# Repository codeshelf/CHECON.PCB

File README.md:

CHECON.PCB
==========

CHE controller PCB design files (No production files/ Brain mounts to this with scanner / PosCon interface etc)

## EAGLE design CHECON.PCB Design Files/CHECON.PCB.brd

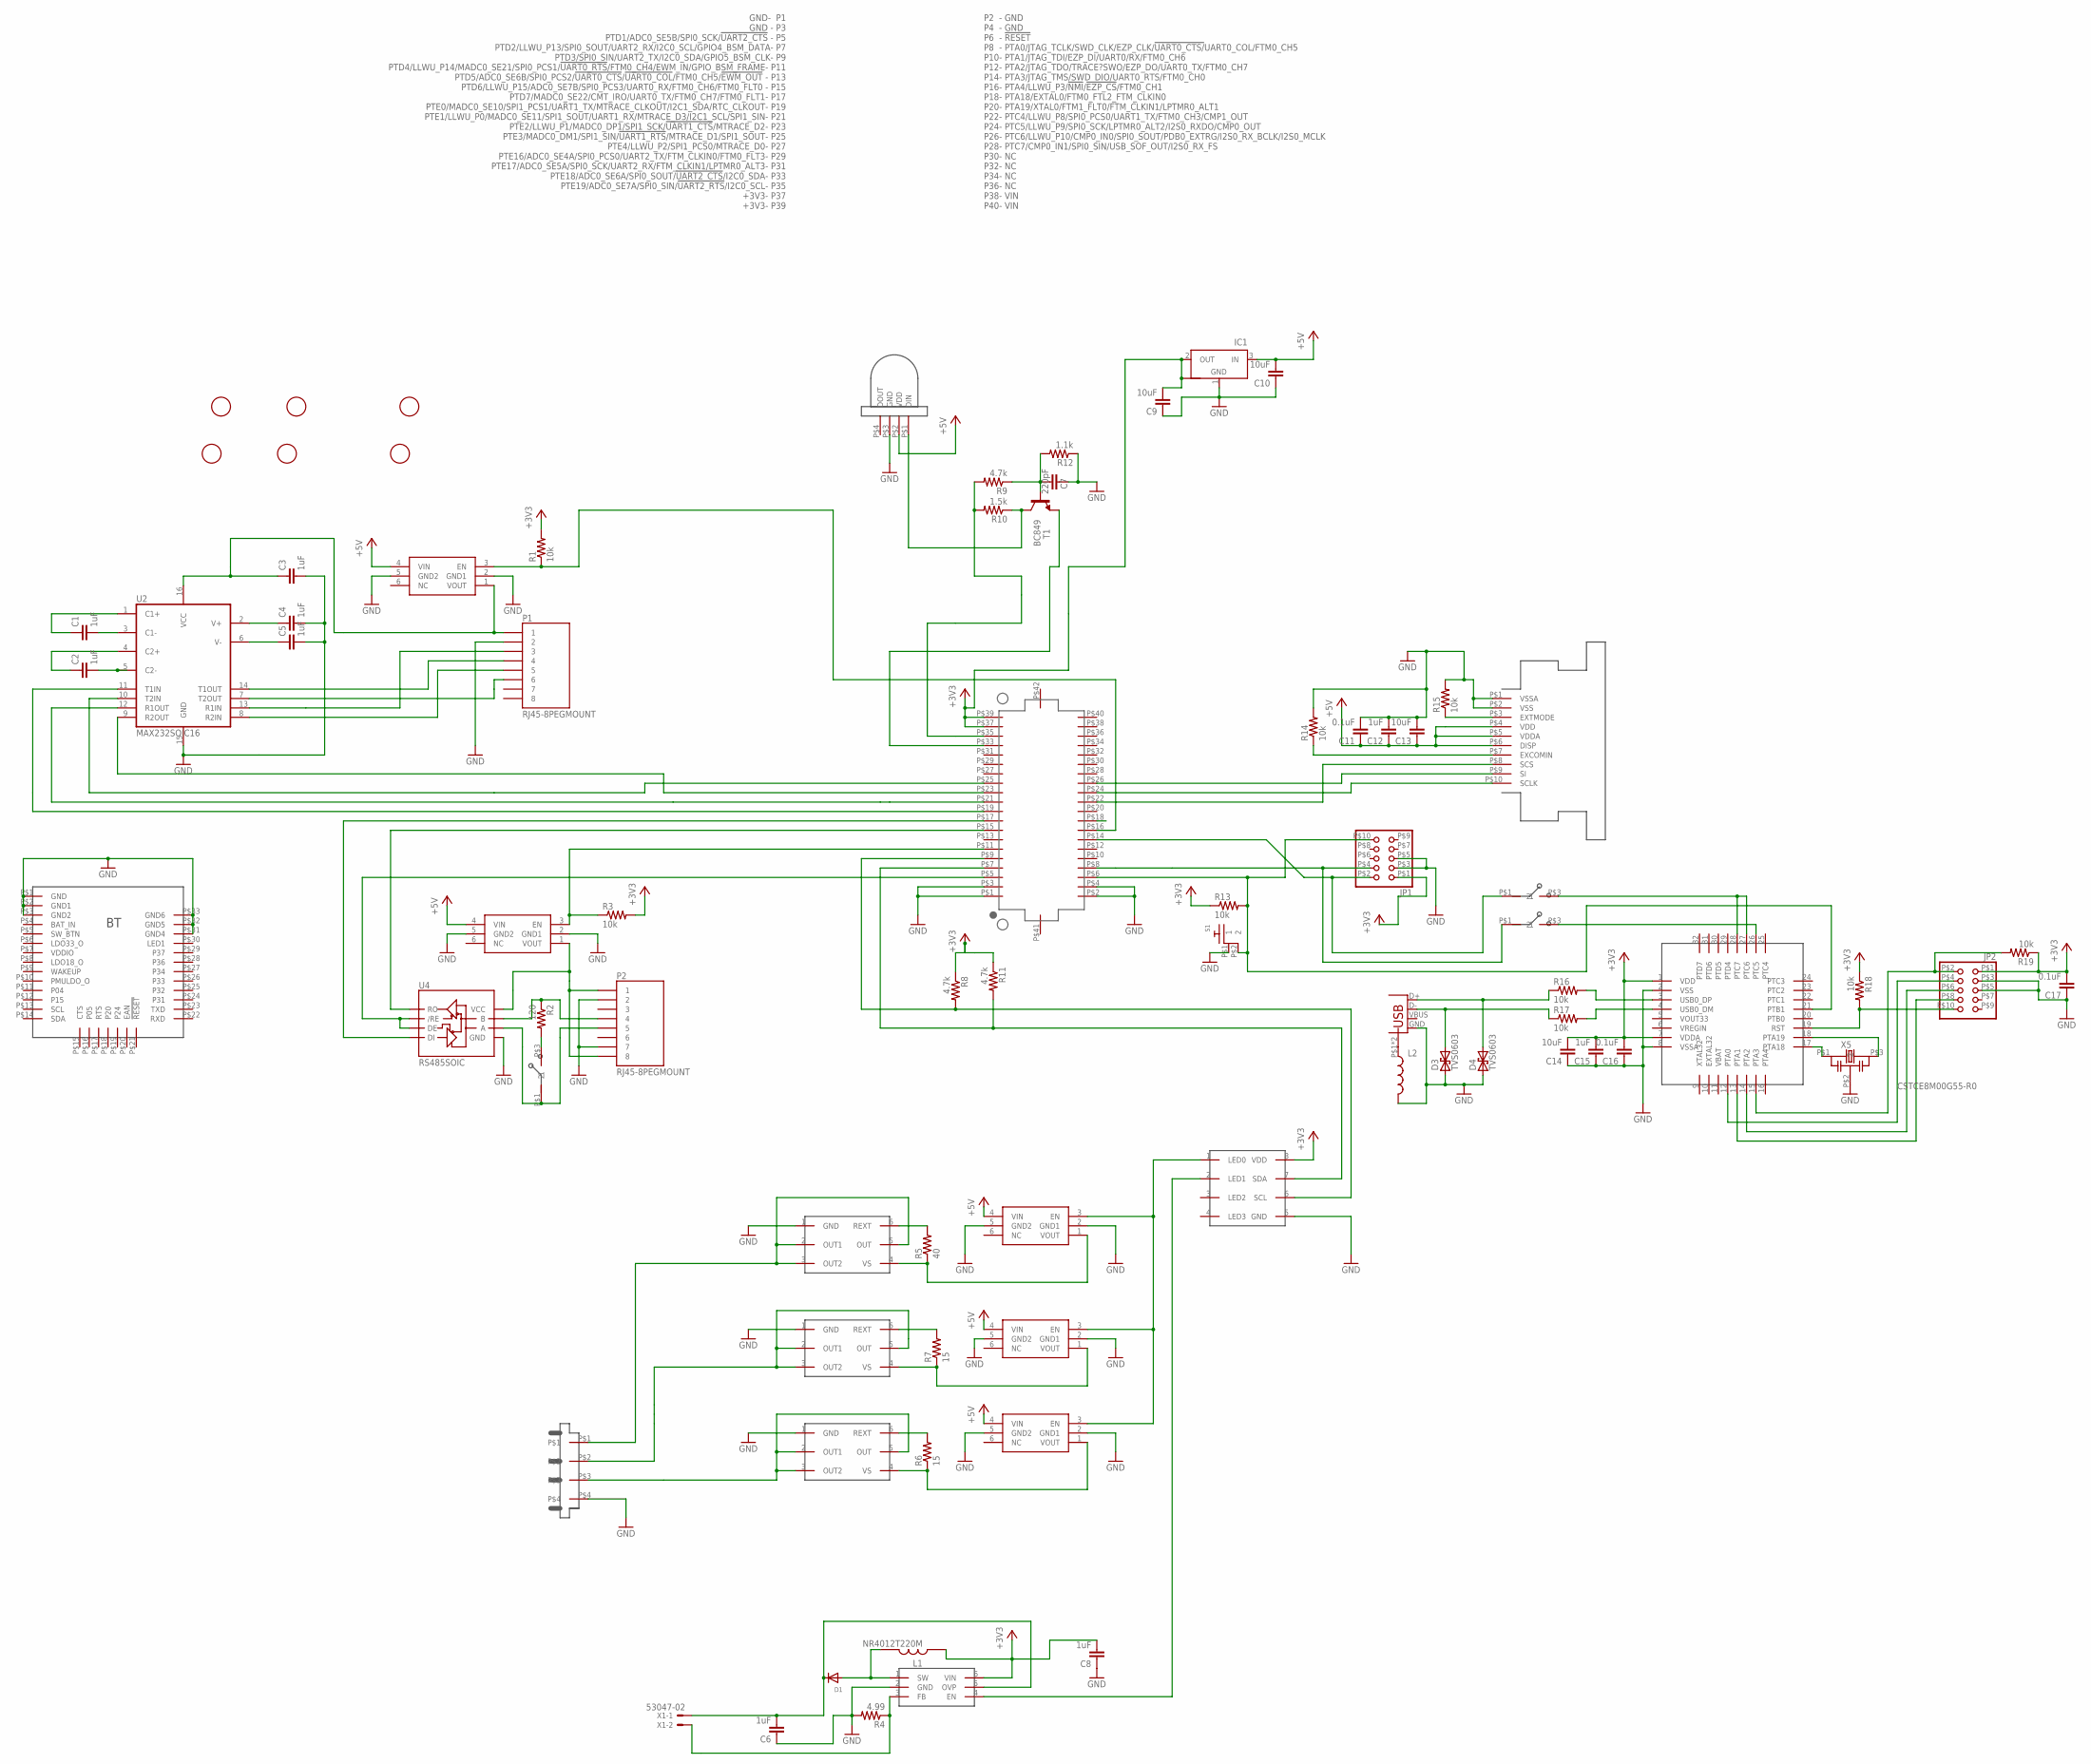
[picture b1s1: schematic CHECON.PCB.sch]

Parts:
C1, C2, C3, C4, C5, C6, C8, C12, C15: 1uF; C0805
C7: 220pF; C0805
C9, C10, C13, C14: 10uF; C0805
C11, C16, C17: 0.1uF; C0805
D1: DIODESOD-523; SOD-523
D2: LED_PTH_2812
D3, D4: TVS0603; 0603-RES
F1, F2, F3, F4, F5, F6: FIDUCIAL; FIDUCIAL_1MM
IC1: NCP1117ST33T3G_1; SOT223
J1: 2.7_BL_CONN; XD2B-0406-26A
J2: USB_B; USB-B-PTH-VERTICAL
J3: 52745-1097
JP1, JP2: PINHD-2X5SMALL; 2X5HDR
L1: NR4012T220M
L2: INDUCTOR0603; 0603
P1, P2: RJ45-8PEGMOUNT; MOLEX-0955016889
R1, R3, R13, R14, R15, R16, R17, R18, R19: 10k; RF-C0805
R2: 120; RF-C0805
R4: 4.99; RF-C0805
R5: 40; RF-C0805
R6, R7: 15; RF-C0805
R8, R9, R11: 4.7k; RF-C0805
R10: 1.5k; RF-C0805
R12: 1.1k; RF-C0805
S1: RA_BUTTON
SW1, SW2, SW3: CJS
T1: BC849; SOT23
U1: BM78
U2: MAX232SOIC16; SO016
U3, U5, U7, U8, U9: MIC94061C6; SC70-6L
U4: RS485SOIC; SO08
U6: AP5724; SOT23-6
U10: KW2_CPU_OFFSET; BRAIN_OFFSET
U11: PCA9632DP1; TSSOP-8
U12: KL20; QFN-32-NOPAD
X1: 53047-02
X2, X3, X4: BCR401U; SOT23-6
X5: CSTCE8M00G55-R0; CSTCE_G_A

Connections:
+3V3: C8.2, C9.2, C14.2, C15.2, C16.2, C17.2, IC1.2 (OUT), IC1.4 (OUT1), JP1.P$1 (1), JP2.P$1 (1), L1.P$2 (2), R1.2, R3.2, R8.1, R11.1, R13.1, R18.1, R19.1, U6.6 (VIN), U10.P$37 (+3V3), U10.P$39 (+3V3), U11.8 (VDD), U12.1 (VDD), U12.7 (VDDA)
+5V: C10.2, D2.P$2 (VDD), IC1.3 (IN), U7.4 (VIN), U8.4 (VIN), U9.4 (VIN)
C1: C1.1, U2.1 (C1+)
C2: C2.1, U2.4 (C2+)
GND: C3.2, C4.2, C5.2, C6.1, C7.1, C8.1, C9.1, C10.1, C11.2, C12.2, C13.2, C14.1, C15.1, C16.1, C17.1, D2.P$3 (GND), D3.1, D4.1, IC1.1 (GND), J1.P$4, J2.GND, J3.P$1 (VSSA), J3.P$2 (VSS), JP1.P$3 (3), JP1.P$5 (5), JP2.P$3 (3), JP2.P$5 (5), L2.2, P1.P$2 (2), P2.P$2 (2), P2.P$7 (7), R4.2, R12.1, R14.2, R15.2, S1.P$1 (1), U1.P$1 (GND), U1.P$2 (GND1), U1.P$3 (GND2), U1.P$31 (GND4), U1.P$32 (GND5), U1.P$33 (GND6), U2.15 (GND), U3.2 (GND1), U3.5 (GND2), U4.5 (GND), U5.2 (GND1), U5.5 (GND2), U6.2 (GND), U7.2 (GND1), U7.5 (GND2), U8.2 (GND1), U8.5 (GND2), U9.2 (GND1), U9.5 (GND2), U10.P$1 (GND), U10.P$2 (GND), U10.P$3 (GND), U10.P$4 (GND), U11.5 (GND), U12.2 (VSS), U12.8 (VSSA), X2.1 (GND), X3.1 (GND), X4.1 (GND), X5.P$2 (2)
unnamed: SW2.P$3 (2), U12.27 (PTC6), U12.28 (PTC7)
unnamed: U6.4 (EN), U11.2 (LED1)
unnamed: R4.1, U6.3 (FB), X1.2
unnamed: U12.17 (PTA18), X5.P$1 (1)
unnamed: J2.P$1 (SHIELD), J2.P$2 (SHIELD), L2.1
unnamed: U12.18 (PTA19), X5.P$3 (3)
unnamed: P1.P$6 (6), U2.7 (T2OUT)
unnamed: J1.P$1, X2.2 (OUT1), X2.3 (OUT2), X2.5 (OUT)
unnamed: U2.12 (R1OUT), U10.P$21 (PTE1/LLWU_P0/MADC0_SE11/SPI1_SOUT/UART1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)
unnamed: R9.2, R10.2, U10.P$35 (PTE19/ADC0_SE7A/SPI0_SIN/!UART2_RTS!/I2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)
unnamed: P1.P$4 (4), U2.14 (T1OUT)
unnamed: R6.1, U9.1 (VOUT), X4.4 (VS)
unnamed: R7.1, U8.1 (VOUT), X3.4 (VS)
unnamed: R5.1, U7.1 (VOUT), X2.4 (VS)
unnamed: T1.2 (E), U10.P$33 (PTE18/ADC0_SE6A/SPI0_SOUT/!UART2_CTS!/I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)
unnamed: U4.1 (RO), U10.P$15 (PTD6/LLWU_P15/ADC0_SE7B/SPI0_PCS3/UART0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)
unnamed: C1.2, U2.3 (C1-)
unnamed: P2.P$4 (4), R2.1, U4.7 (B)
unnamed: P2.P$5 (5), SW1.P$1 (1), U4.6 (A)
unnamed: C2.2, U2.5 (C2-)
unnamed: C5.1, U2.6 (V-)
unnamed: C4.1, U2.2 (V+)
unnamed: R16.2, U12.3 (USB0_DP)
unnamed: C3.1, P1.P$1 (1), U2.16 (VCC), U3.1 (VOUT)
unnamed: U2.11 (T1IN), U10.P$19 (PTE0/MADC0_SE10/SPI1_PCS1/UART1_TX/MTRA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)
unnamed: U4.4 (DI), U10.P$17 (PTD7/MADC0_SE22/CMT_IRO/UART0_TX/FTM0_C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)
unnamed: U4.2 (/RE), U4.3 (DE), U10.P$5 (PTD1/ADC0_SE5B/SPI0_SCK/!UART2_CTS)
unnamed: J3.P$9 (SI), U10.P$26 (PTC6/LLWU_P10/CMP0_IN0/SPI0_SOUT/PDB0_E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)
unnamed: J3.P$10 (SCLK), U10.P$24 (PTC5/LLWU_P8/SPI0_PCS0/UART1_TX/FTM0_CH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)
unnamed: J3.P$8 (SCS), U10.P$22 (PTC4/LLWU_P8/SPI0_PCS0/UART1_TX/FTM0_CH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)
unnamed: J3.P$3 (EXTMODE), R15.1
unnamed: J3.P$7 (EXCOMIN), R14.1
unnamed: P1.P$5 (5), U2.8 (R2IN)
unnamed: D3.2, J2.D-, R17.1
unnamed: D4.2, J2.D+, R16.1
unnamed: R6.2, X4.6 (REXT)
unnamed: U2.9 (R2OUT), U10.P$23 (PTE2/LLWU_P1/MADC0_DP1/SPI1_SCK/!UART1_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)
unnamed: R3.1, U5.3 (EN), U10.P$11 (PTD4/LLWU_P14/MADC0_SE21/SPI0_PCS1/!UAR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)
unnamed: R1.1, U3.3 (EN), U10.P$16 (PTA4/LLWU_P3/!NMI!/!EZP_CS!/FTM0_CH1)
unnamed: U2.10 (T2IN), U10.P$25 (PTE3/MADC0_DM1/SPI1_SIN/!UART1_RTS!/MTR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)
unnamed: R7.2, X3.6 (REXT)
unnamed: R5.2, X2.6 (REXT)
unnamed: U7.3 (EN), U8.3 (EN), U9.3 (EN), U11.1 (LED0)
unnamed: R11.2, U10.P$7 (PTD2/LLWU_P13/SPI0_SOUT/UART2_RX/I2C0_S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), U11.7 (SDA)
unnamed: R8.2, U10.P$9 (PTD3/SPI0_SIN/UART2_TX/I2C0_SDA/GPIO5_B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), U11.6 (SCL)
unnamed: D2.P$1 (DIN), R10.1, T1.3 (C)
unnamed: C7.2, R9.1, R12.2, T1.1 (B)
unnamed: D1.A, L1.P$1 (1), U6.1 (SW)
unnamed: J1.P$3, X4.2 (OUT1), X4.3 (OUT2), X4.5 (OUT)
unnamed: JP2.P$2 (2), R19.2, U12.15 (PTA3)
unnamed: J1.P$2, X3.2 (OUT1), X3.3 (OUT2), X3.5 (OUT)
unnamed: C6.2, D1.K (C), U6.5 (OVP), X1.1
unnamed: JP2.P$4 (4), U12.12 (PTA0)
unnamed: JP2.P$6 (6), U12.14 (PTA2)
unnamed: JP2.P$8 (8), U12.13 (PTA1)
unnamed: JP2.P$10 (10), R18.2, U12.19 (RST)
unnamed: R2.2, SW1.P$3 (2)
unnamed: R17.2, U12.4 (USB0_DM)
R1IN: P1.P$3 (3), U2.13 (R1IN)
RST: JP1.P$10 (10), R13.2, S1.P$2 (2), U10.P$6 (!RESET), U12.21 (PTB1)
SWD_CLK: JP1.P$4 (4), SW3.P$1 (1), U10.P$8 (PTA0/JTAG_TCLK/SWD_CLK/EZP_CLK/!UART0_C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)
SWD_DIO: JP1.P$2 (2), SW2.P$1 (1), U10.P$14 (PTA3/JTAG_TMS/SWD_DIO/UART0_RTS/FTM0_CH0)
SWD_TGT_CLK: SW3.P$3 (2), U12.26 (PTC5)
V+: C11.1, C12.1, C13.1, J3.P$4 (VDD), J3.P$5 (VDDA), J3.P$6 (DISP), P2.P$1 (1), P2.P$8 (8), U3.4 (VIN), U4.8 (VCC), U5.1 (VOUT), U5.4 (VIN)

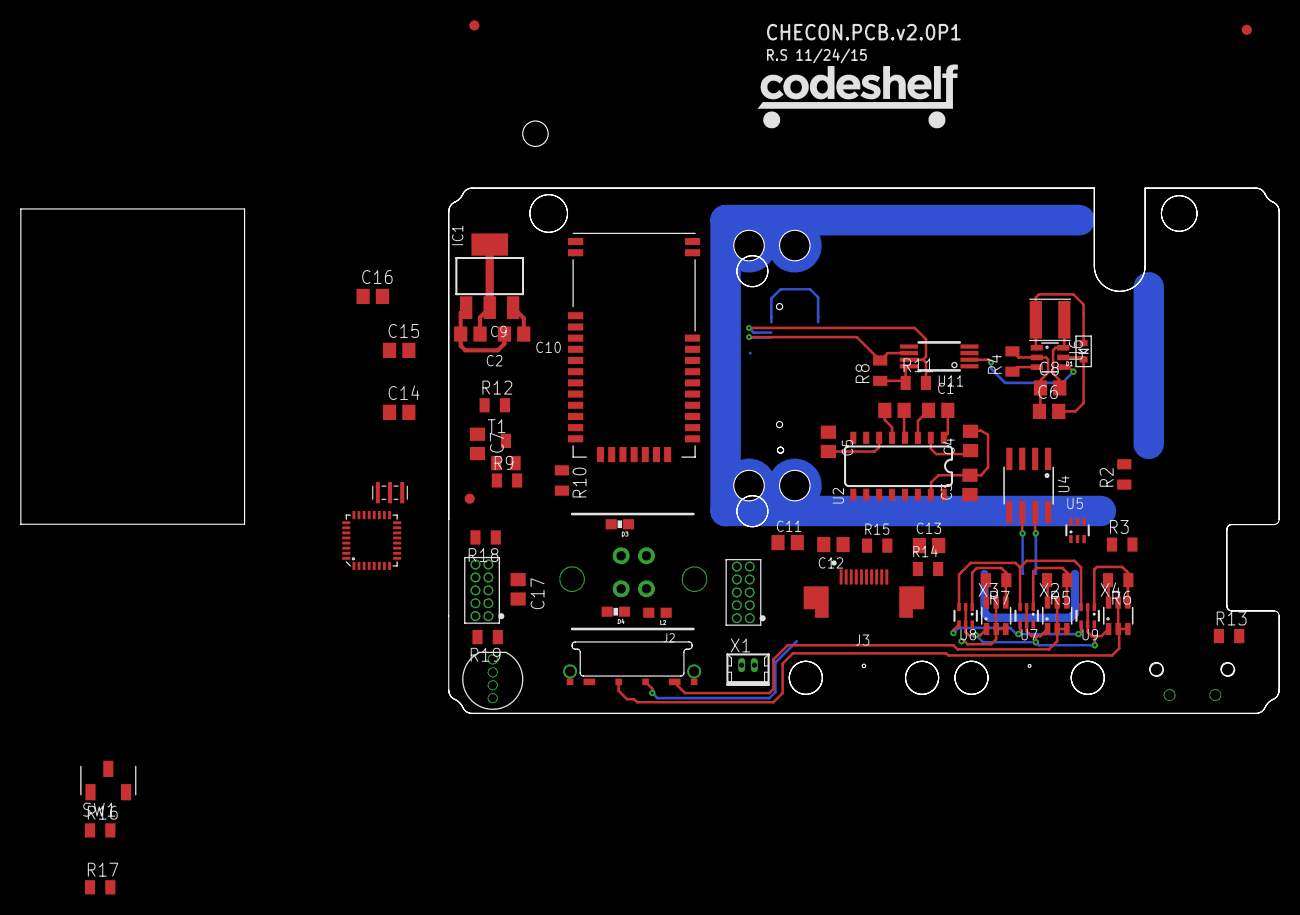
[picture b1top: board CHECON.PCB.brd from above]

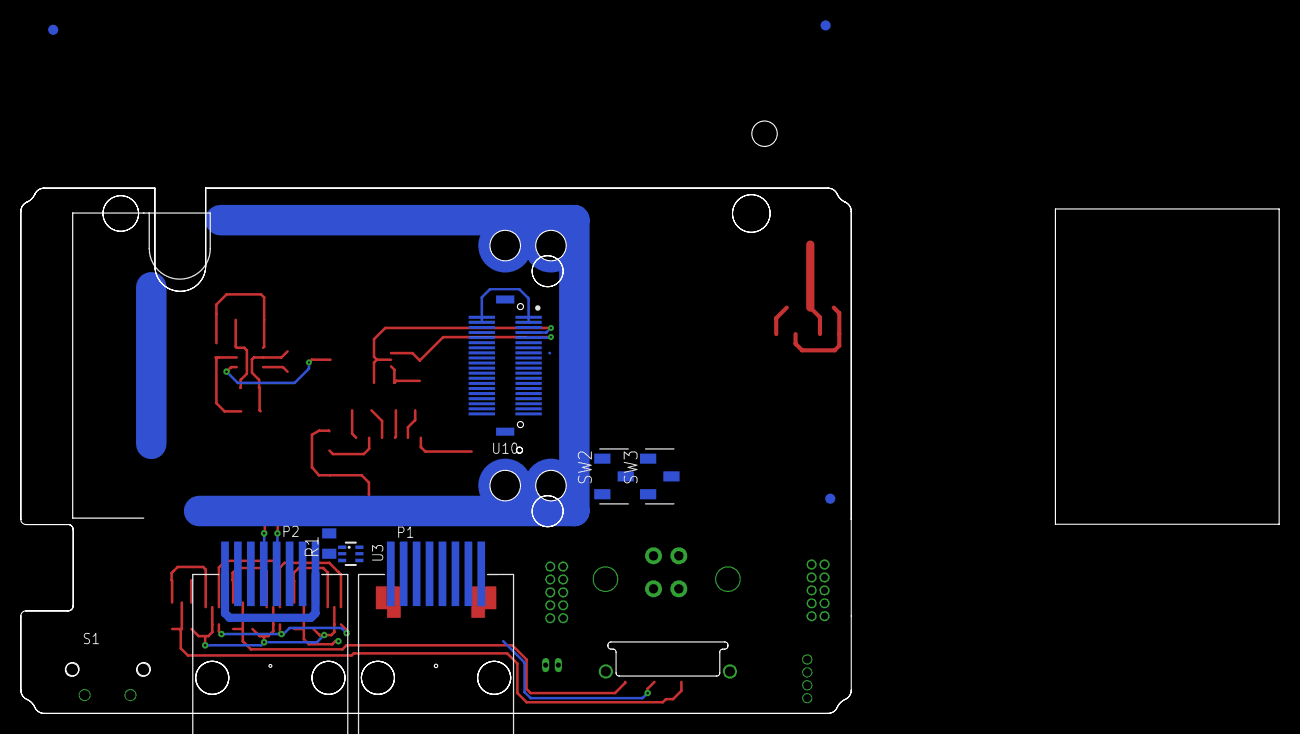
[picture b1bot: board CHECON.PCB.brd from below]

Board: 2 copper layers, 81.7 x 51.6 mm, 78 parts (11 on the bottom side), 69 nets.

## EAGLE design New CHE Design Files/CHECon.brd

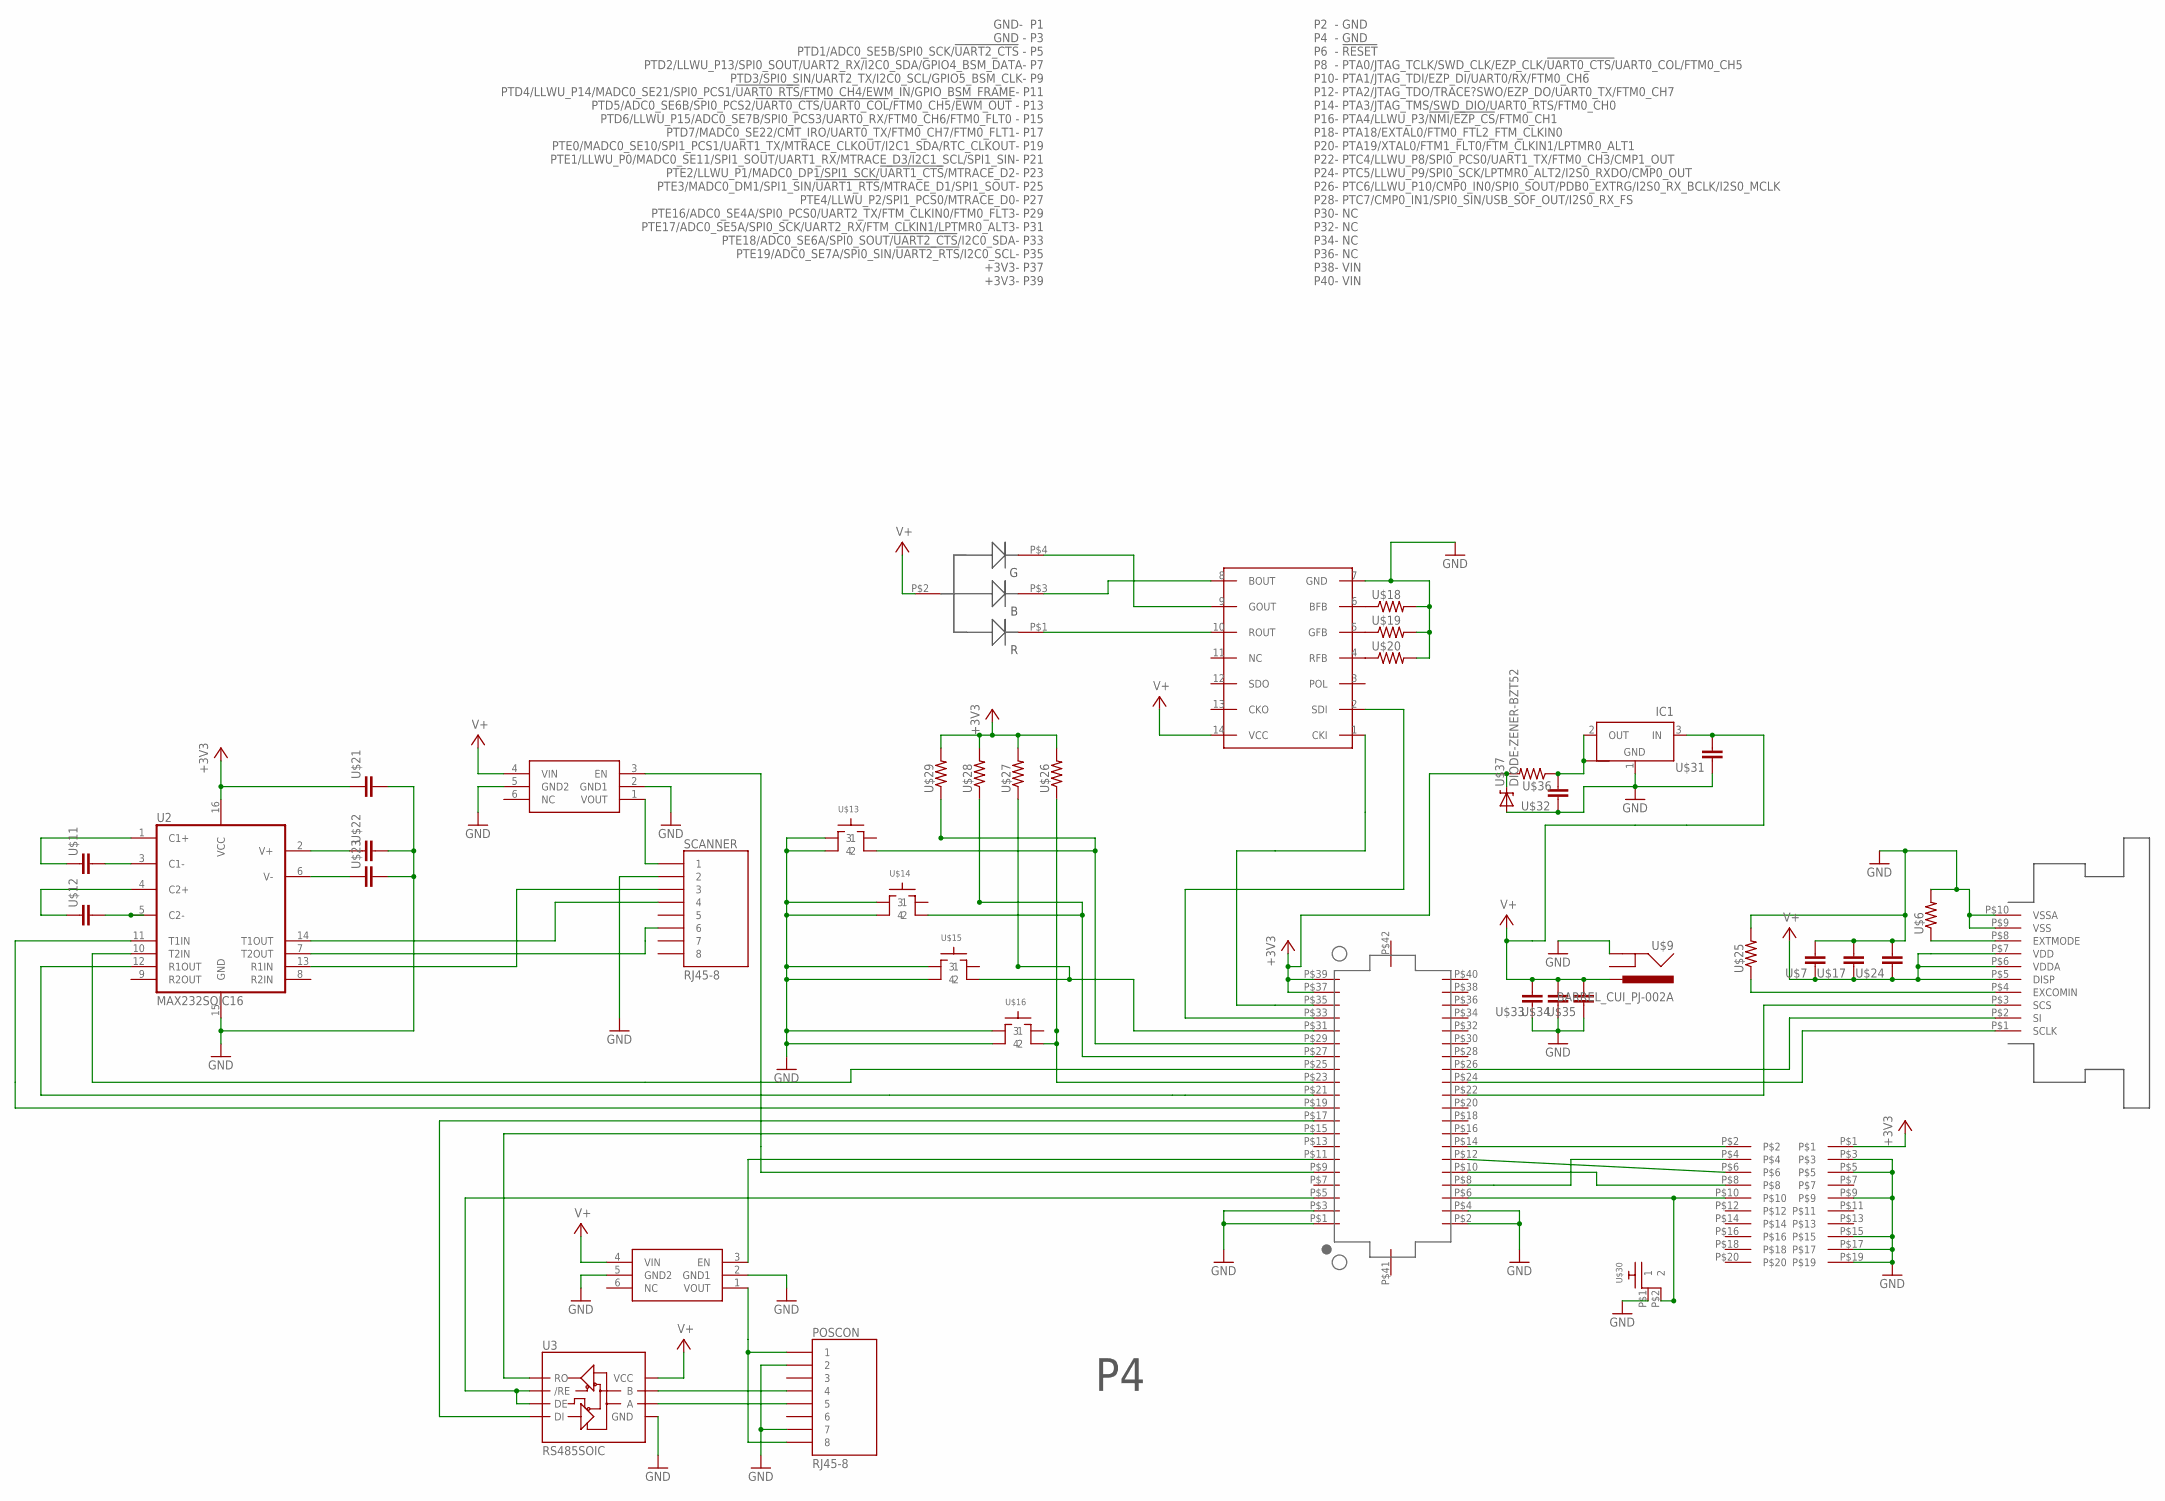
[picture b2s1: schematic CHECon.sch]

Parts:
IC1: NCP1117ST33T3G_1; SOT223
POSCON: RJ45-8; MOLEX-0955016649
SCANNER: RJ45-8; MOLEX-0955016649
U2: MAX232SOIC16; SO016
U3: RS485SOIC; SO08
U$1: RGLBED; RGBLED
U$2: 52745-1097
U$3: 2X10JTAG
U$4, U$5: MIC94061C6; SC70-6L
U$6, U$18, U$19, U$20, U$25, U$26, U$27, U$28, U$29, U$36: RF-R0805; RF-C0805
U$7, U$11, U$12, U$17, U$21, U$22, U$23, U$24, U$31, U$32, U$33, U$34, U$35: RF-C0805; C0805
U$8: WS2801; SO14
U$9: BARREL_CUI_PJ-002A
U$10: DF12_F
U$13, U$14, U$15, U$16: SWITCH-TACTILE; ESWITCH-TL3301PF
U$30: RA_BUTTON
U$37: DIODE-ZENER-BZT52; SOD-323

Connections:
+3V3: U2.16 (VCC), U$3.P$1, U$10.P$37 (+3V3), U$10.P$39 (+3V3), U$21.1, U$26.2, U$27.2, U$28.2, U$29.2, U$36.2, U$37.1 (C)
C1: U2.1 (C1+), U$11.1
C2: U2.4 (C2+), U$12.1
GND: IC1.1 (GND), POSCON.P$2 (2), POSCON.P$7 (7), SCANNER.P$2 (2), U2.15 (GND), U3.5 (GND), U$2.P$9 (VSS), U$2.P$10 (VSSA), U$3.P$3, U$3.P$5, U$3.P$9, U$3.P$15, U$3.P$17, U$3.P$19, U$4.2 (GND1), U$4.5 (GND2), U$5.2 (GND1), U$5.5 (GND2), U$6.2, U$7.2, U$8.7 (GND), U$9.P$2 (GND), U$10.P$1 (GND), U$10.P$2 (GND), U$10.P$3 (GND), U$10.P$4 (GND), U$13.1, U$13.2, U$14.1, U$14.2, U$15.1, U$15.2, U$16.1, U$16.2, U$17.2, U$18.2, U$19.2, U$20.2, U$21.2, U$22.2, U$23.2, U$24.2, U$25.2, U$30.P$1 (1), U$31.1, U$32.1, U$33.1, U$34.1, U$35.1, U$37.2 (A)
unnamed: U$3.P$2, U$10.P$14 (PTA3/JTAG_TMS/SWD_DIO/UART0_RTS/FTM0_CH0)
unnamed: U$3.P$6, U$10.P$12 (PTA2/JTAG_TDO/TRACE?SWO/EZP_DO/UART0_TX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)
unnamed: U$3.P$8, U$10.P$10 (PTA1/JTAG_TDI/EZP_DI/UART0/RX/FTM0_CH6)
unnamed: U$3.P$4, U$10.P$8 (PTA0/JTAG_TCLK/SWD_CLK/EZP_CLK/!UART0_C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)
unnamed: U$1.P$4 (GREEN), U$8.9 (GOUT)
unnamed: U$3.P$10, U$10.P$6 (!RESET), U$30.P$2 (2)
unnamed: SCANNER.P$6 (6), U2.7 (T2OUT)
unnamed: U$1.P$3 (BLUE), U$8.8 (BOUT)
unnamed: U$1.P$1 (RED), U$8.10 (ROUT)
unnamed: U2.12 (R1OUT), U$10.P$21 (PTE1/LLWU_P0/MADC0_SE11/SPI1_SOUT/UART1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)
unnamed: U$8.1 (CKI), U$10.P$35 (PTE19/ADC0_SE7A/SPI0_SIN/!UART2_RTS!/I2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)
unnamed: SCANNER.P$4 (4), U2.14 (T1OUT)
unnamed: U$8.6 (BFB), U$18.1
unnamed: U$8.5 (GFB), U$19.1
unnamed: U$8.4 (RFB), U$20.1
unnamed: U$8.2 (SDI), U$10.P$33 (PTE18/ADC0_SE6A/SPI0_SOUT/!UART2_CTS!/I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)
unnamed: U3.1 (RO), U$10.P$15 (PTD6/LLWU_P15/ADC0_SE7B/SPI0_PCS3/UART0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)
unnamed: U2.3 (C1-), U$11.2
unnamed: POSCON.P$4 (4), U3.7 (B)
unnamed: POSCON.P$5 (5), U3.6 (A)
unnamed: U2.5 (C2-), U$12.2
unnamed: U2.6 (V-), U$23.1
unnamed: U2.2 (V+), U$22.1
unnamed: POSCON.P$1 (1), POSCON.P$8 (8), U$5.1 (VOUT)
unnamed: SCANNER.P$1 (1), U$4.1 (VOUT)
unnamed: U2.11 (T1IN), U$10.P$19 (PTE0/MADC0_SE10/SPI1_PCS1/UART1_TX/MTRA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)
unnamed: U3.4 (DI), U$10.P$17 (PTD7/MADC0_SE22/CMT_IRO/UART0_TX/FTM0_C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)
unnamed: U3.2 (/RE), U3.3 (DE), U$10.P$5 (PTD1/ADC0_SE5B/SPI0_SCK/!UART2_CTS)
unnamed: U$2.P$2 (SI), U$10.P$26 (PTC6/LLWU_P10/CMP0_IN0/SPI0_SOUT/PDB0_E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)
unnamed: U$2.P$1 (SCLK), U$10.P$24 (PTC5/LLWU_P8/SPI0_PCS0/UART1_TX/FTM0_CH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)
unnamed: U$2.P$3 (SCS), U$10.P$22 (PTC4/LLWU_P8/SPI0_PCS0/UART1_TX/FTM0_CH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)
unnamed: U$2.P$8 (EXTMODE), U$6.1
unnamed: U$2.P$4 (EXCOMIN), U$25.1
unnamed: U$10.P$23 (PTE2/LLWU_P1/MADC0_DP1/SPI1_SCK/!UART1_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), U$16.4, U$26.1
unnamed: U$10.P$31 (PTE17/ADC0_SE5A/SPI0_SCK/UART2_RX/FTM_C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), U$15.4, U$27.1
unnamed: U$10.P$27 (PTE4/LLWU_P2/SPI1_PCS0/MTRACE_D0), U$14.4, U$28.1
unnamed: U$10.P$29 (PTE16/ADC0_SE4A/SPI0_PCS0/UART2_TX/FTM_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), U$13.4, U$29.1
unnamed: U$5.3 (EN), U$10.P$11 (PTD4/LLWU_P14/MADC0_SE21/SPI0_PCS1/!UAR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)
unnamed: U$4.3 (EN), U$10.P$9 (PTD3/SPI0_SIN/UART2_TX/I2C0_SCL/GPIO5_B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)
unnamed: U2.10 (T2IN), U$10.P$25 (PTE3/MADC0_DM1/SPI1_SIN/!UART1_RTS!/MTR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)
OUT1: IC1.2 (OUT), IC1.4 (OUT1), U$32.2, U$36.1
R1IN: SCANNER.P$3 (3), U2.13 (R1IN)
V+: IC1.3 (IN), U3.8 (VCC), U$1.P$2 (ANODE), U$2.P$5 (DISP), U$2.P$6 (VDDA), U$2.P$7 (VDD), U$4.4 (VIN), U$5.4 (VIN), U$7.1, U$8.14 (VCC), U$9.P$1 (PWR), U$17.1, U$24.1, U$31.2, U$33.2, U$34.2, U$35.2

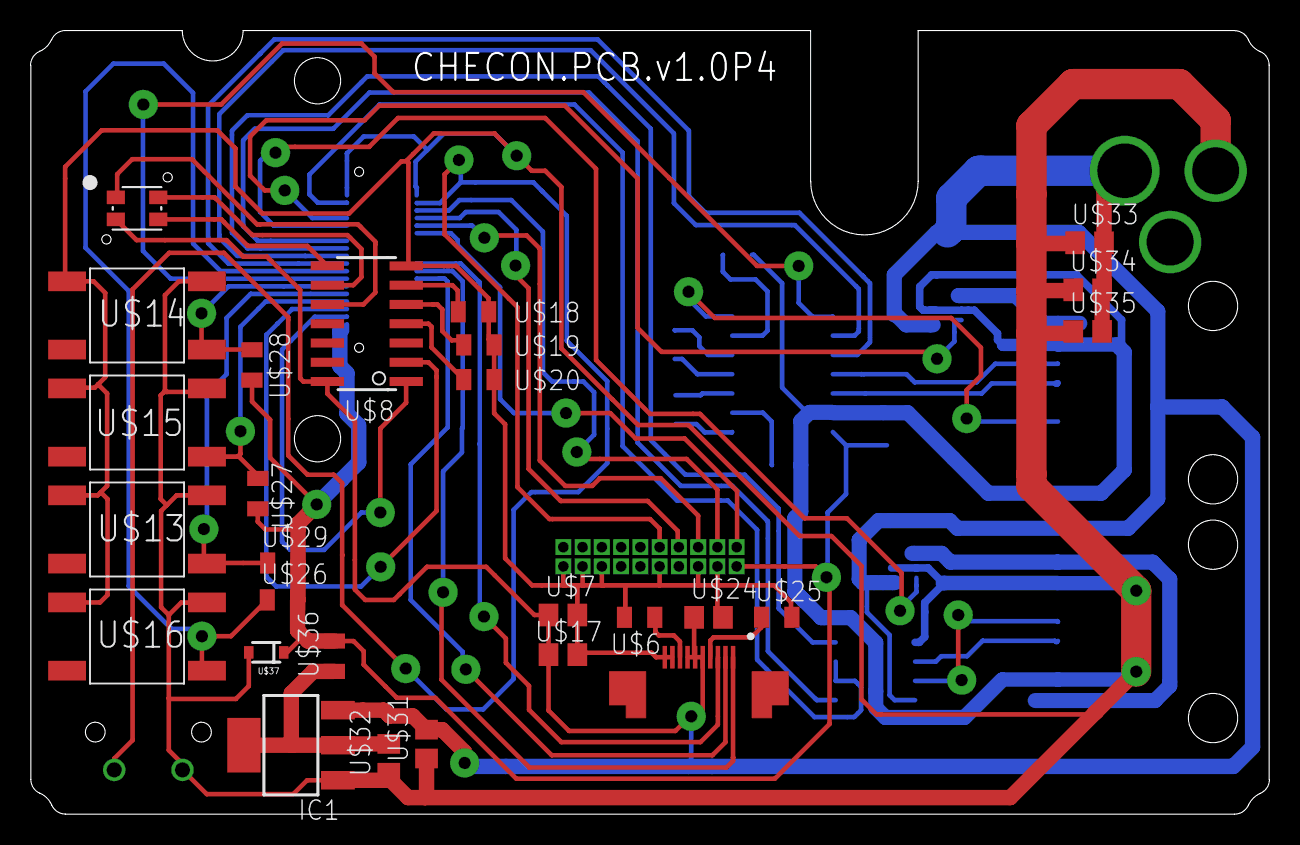
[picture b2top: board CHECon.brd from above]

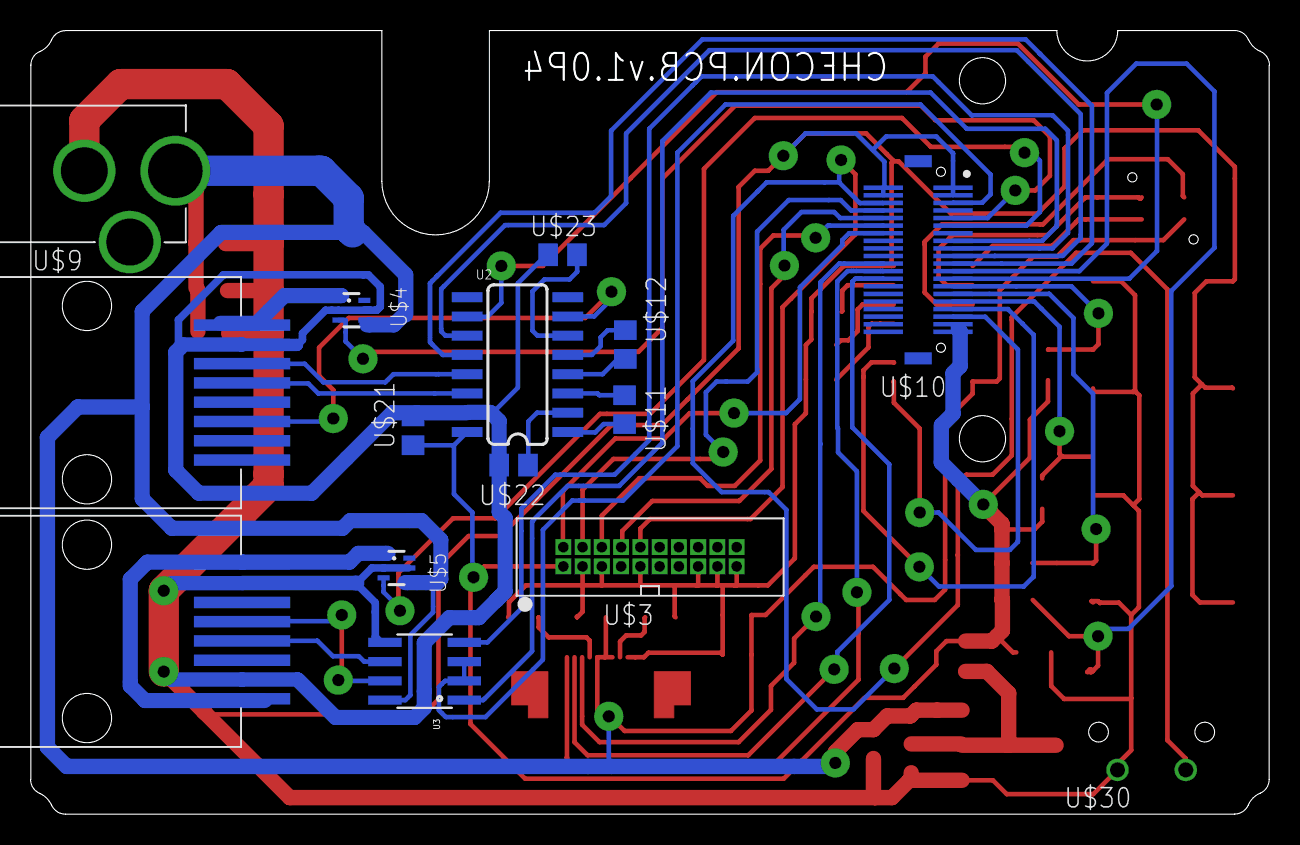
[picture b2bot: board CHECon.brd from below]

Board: 2 copper layers, 81.7 x 51.7 mm, 42 parts (15 on the bottom side), 47 nets.

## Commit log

2015-01-17 Finished (?) schematic (P1?)
    First version, hopefully complete schematic.
2015-01-28 P1
    P1, seems to have errors
2015-01-28 Updated FPC
    Pin names
2015-01-30 P2
    Fixed LED, reset switch, scanner RTS, flipped FPC
2015-02-03 P3 - in progress
    Added 0.4mm spacing, need level shifter and other screen changes
2015-02-11 P3
    Added VR and Zener just in case
2015-02-19 P4
    Fixed MAX232 rail, moved to 3.3V
2015-02-19 P4 update
    Moved scanner power select to PTD3 to avoid conflict with EEPROM CS
2015-02-20 CHECON.PCB.v1.0 pre-release
    Pending checklist processing.
    Added all part and manufacturer numbers, fiducials, silkscreen
    labelling, BOM, ECO, FAB notes, Gerber files (+ drill and centroid)
2015-02-23 CHECON.PCB.V1.0
    Fixed some pin 1 markers, grounded unused input on 232, package names,
    flipped FPC pins to correct pin 1 location
2015-07-01 Backlight Routing
    Added backlight drivers and power monitoring. Mid-routing.
2015-07-02 Routing
2015-07-08 Finished layout pending spring connector
    Waiting for physical location of BL connector
2015-07-14 v1.1P1
    Submitted to Chris. Forgot bus terminator
2015-07-14 Added bus terminator to schematic
    Still need to add to layout
2015-09-30 Through-hole switch?
    Replaced buttons with though-hole versions (I think)
2015-09-30 Pull-ups and terminator
    Added pull-ups to Micrel switches and RS485 Bus terminator
2015-11-25 CHECON_2.7.v1.1P2 (?)
    Naming debatable. Cut version of v1.1P1, no major changes AFAIK. Changed
    design name, not reflected in current LPKF files.
2015-12-11 New CHE
    Starting on new CHE
2015-12-17 Updated KW2 footprint in design
    Swapped footprint for one with 3mm foam outline
2016-01-08 sync repo
    Sync work while rafael was out
2016-01-15 Minor changes
    Renamed some nets and worked on SWD section
2016-01-29 Working on layout
    Layout
